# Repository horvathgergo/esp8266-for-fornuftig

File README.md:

Newer version of the board based on an ESP32-C6 chip is available here: https://github.com/horvathgergo/esp32c6-for-fornuftig

# Smart Air Purifier (Project Fornuftig)

Custom PCB based on ESP12-F (ESP8266) wifi module that serves as a smart controller for IKEA Fornuftig Air Purifiers. It's embedded microcontroller enables you to incorporate your device to home automation systems (preferably to Home Assistant) or control it via custom mobile applications as it enjoys support from wide variety of firmwares. This project has been implemented in KiCad (hardware) and in Micropython (sofware).

About IKEA Fornuftig: It's a compact, 31x45 cm air purifier launched in the market around 2020. It effectively cleans the indoor air from harmful PM2.5 particles and pollen for a reasonable price (approx. EUR60). The device is optimised for medium-sized bedrooms and has three fan speed. 

Current status of the development: **Finalized**

Hardware: 
* [x] Schematic
* [x] Layout
* [x] BOM, CPL
* [x] 3D model 
* [x] Testing (v1.1 w/o switch)

Software:
* [x] MicroPython

## Hardware

PCB is a bit larger than the original one (98x40 mm) with mounting holes placed on it, thus it is supposed to fit just fine inside the plastic housing. Power supply of the fan is +24V, 0.8A. The board has a MC34063DR switching voltage regulator that provides the necessary power (+3v3, avg 70mA, peak >500mA) for the wifi module. This version (v2.0) of the board is designed with a rotary switch. To avoid unnecessary costs and save some space on the board physical filter reset button is not incorporated in this version as this function can be easily achieved through software side. 

The Purifier has a 4-pin PWM fan with +24VDC, 0.5A. The pins are power, ground, clk, fg. Clk is a control pin and fg is the tacho pin for feedback purposes. The fan operates with a constant duty cycle of 50% and variable frequency between ca. 1-300Hz.

MCU programming: the board supports only UART programming via TX, RX pin headers (as no USB interface), thus USB to TTL converter is necessary to upload your firmware. It is recommended to supply the module via VIN and GND pins during initial setup. It is compatible with +5-24V supply (note: in serial bootloader mode you need to supply at least +5V. Standard +3v3 won't work as you may experience some voltage drop via the buck converter so make sure to provide enough voltage during flashing. Supplying +5V won't hurt the ESP as the VIN pin of the board is not directly connected to chip). Boot button is located on the right side of the wifi module.

Tested first version of the board w/o rotary switch:

BOM: Most of the chosen components are considered to be basic/standard parts at LCSC, however there are some extended components on the list (two large caps, inductor, esp, jst connectors and uart pin headers).

## Software

The software for Fornuftig has been developed in Micropython. It enables the device to be controlled via mqtt while exploits Home Assistant mqtt autodiscovery features that provides with a smooth (almost zero config) setup process.

More detailed description is available in this repo: https://github.com/horvathgergo/uPurifier

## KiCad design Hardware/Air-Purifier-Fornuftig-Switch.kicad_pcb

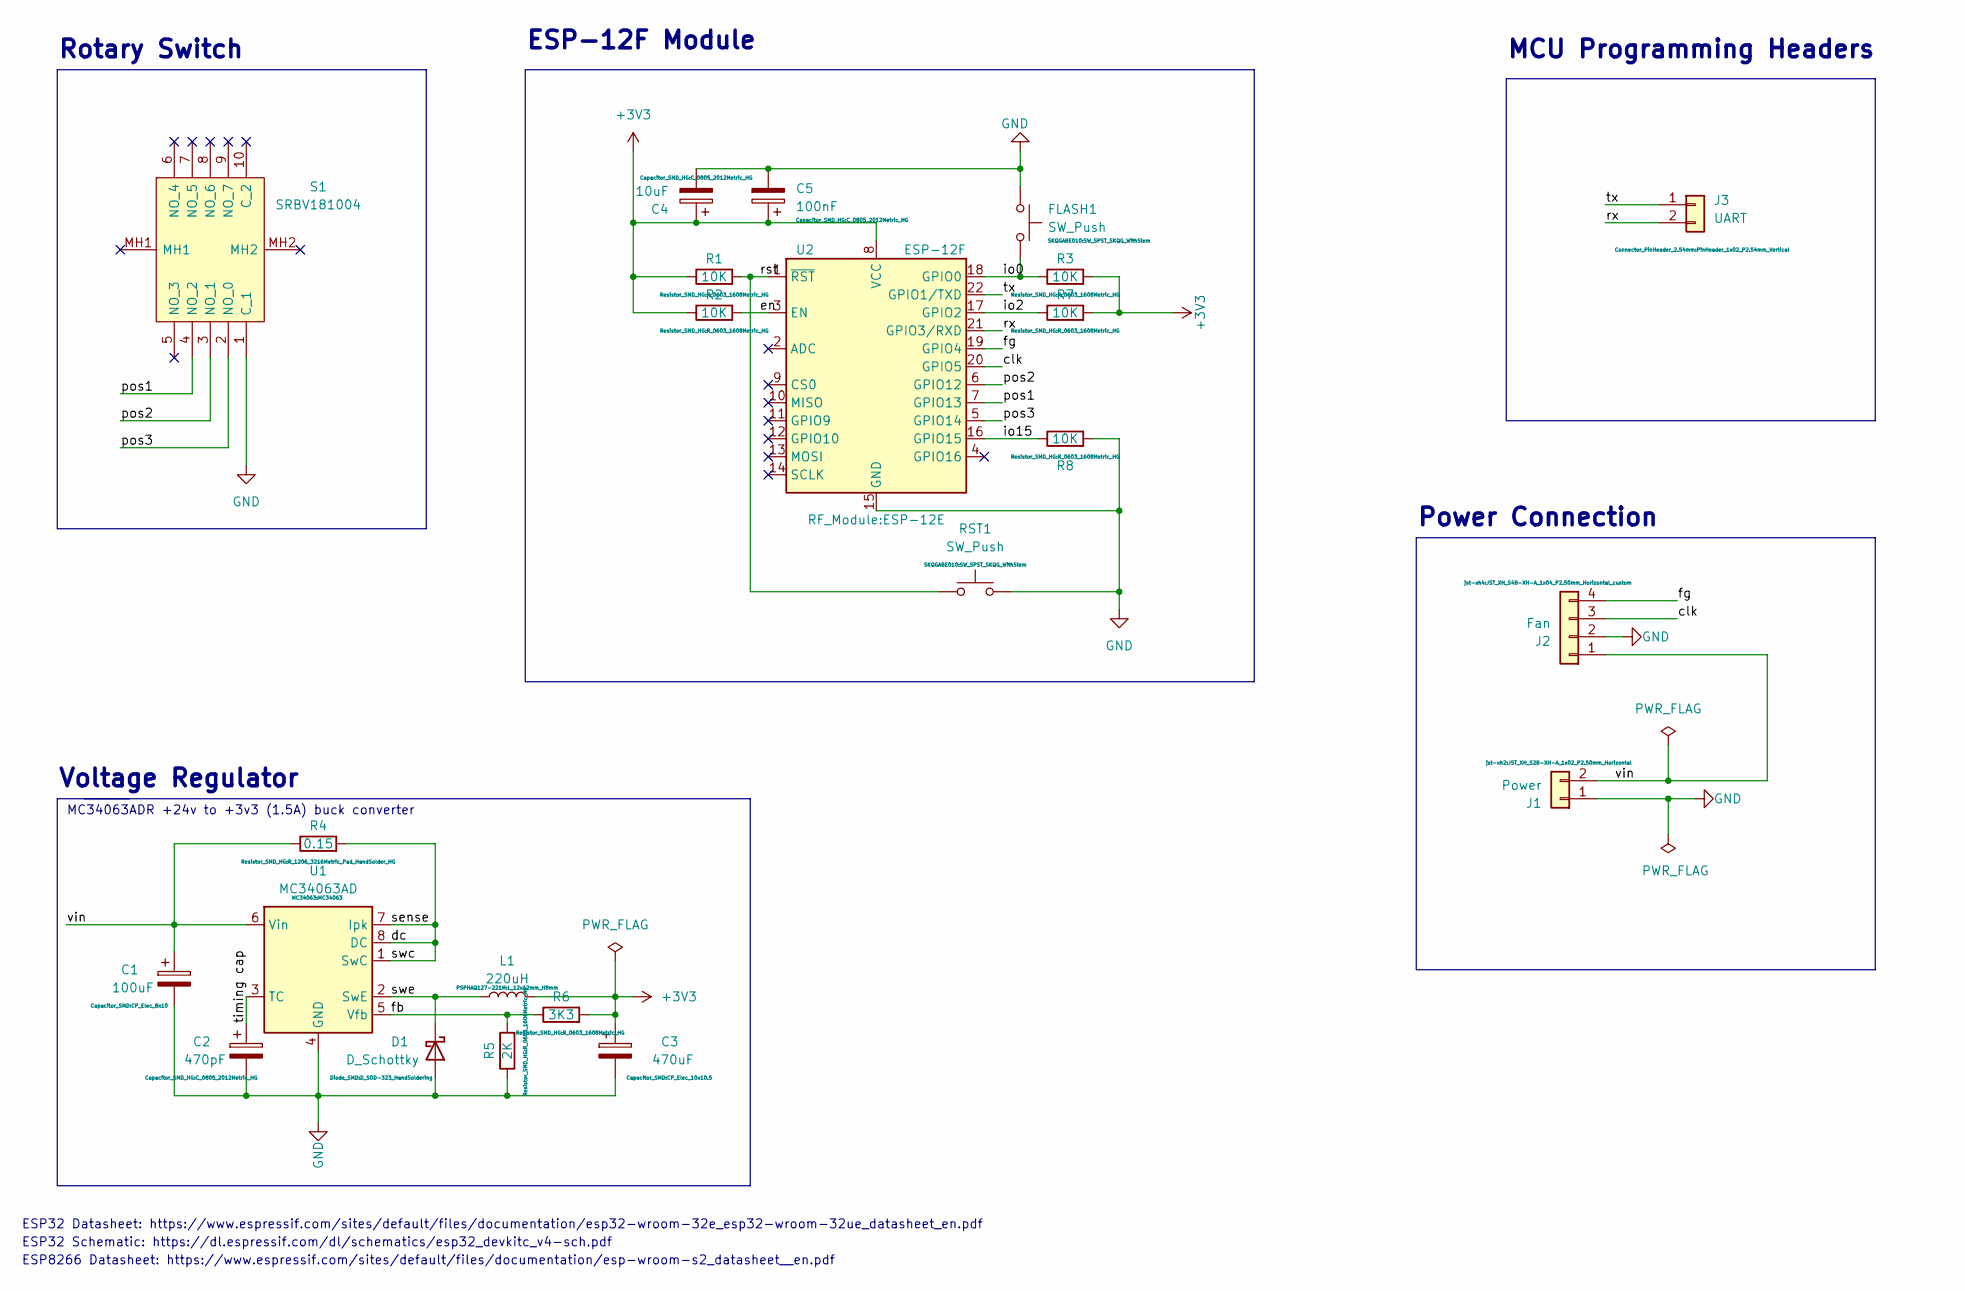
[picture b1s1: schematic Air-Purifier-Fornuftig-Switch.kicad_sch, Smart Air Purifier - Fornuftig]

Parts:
C1: 100uF; CP_Elec_8x10; LCSC C445063
C2: 470pF; C_0805_2012Metric_HG; LCSC C1743
C3: 470uF; CP_Elec_10x10.5; LCSC C72518
C4: 10uF; C_0805_2012Metric_HG; LCSC C15850
C5: 100nF; C_0805_2012Metric_HG; LCSC C28233
D1: D_Schottky; D_SOD-323_HandSoldering; LCSC C191023
FLASH1: SW_Push; SW_SPST_SKQG_WithStem; LCSC C318884
J1: Power; JST_XH_S2B-XH-A_1x02_P2.50mm_Horizontal
J2: Fan; JST_XH_S4B-XH-A_1x04_P2.50mm_Horizontal_custom
J3: UART; PinHeader_1x02_P2.54mm_Vertical
L1: 220uH; L_12x12mm_H8mm; LCSC C10151
R1, R2, R3, R7, R8: 10K; R_0603_1608Metric_HG; LCSC C25804
R4: 0.15; R_1206_3216Metric_Pad_HandSolder_HG; LCSC C247454
R5: 2K; R_0603_1608Metric_HG; LCSC C22975
R6: 3K3; R_0603_1608Metric_HG; LCSC C22978
RST1: SW_Push; SW_SPST_SKQG_WithStem; LCSC C318884
S1: SRBV181004; SRBV141404; Manufacturer_Part_Number SRBV181004; Mouser Part Number 688-SRBV181004
U1: MC34063AD; MC34063; LCSC C32078
U2: ESP-12F; ESP-12E; LCSC C82891

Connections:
+3V3: C3.1, C4.1, C5.1, L1.2, R1.1, R2.1, R3.2, R6.2, R7.2, U2.8 (VCC)
/clk: J2.3, U2.20 (GPIO5)
/dc: R4.2, U1.1 (SwC), U1.7 (Ipk), U1.8 (DC)
/en: R2.2, U2.3 (EN)
/fb: R5.2, R6.1, U1.5 (Vfb)
/fg: J2.4, U2.19 (GPIO4)
/io0: FLASH1.2, R3.1, U2.18 (GPIO0)
/io2: R7.1, U2.17 (GPIO2)
/io15: R8.1, U2.16 (GPIO15)
/pos1: S1.4 (NO_2), U2.7 (GPIO13)
/pos2: S1.3 (NO_1), U2.6 (GPIO12)
/pos3: S1.2 (NO_0), U2.5 (GPIO14)
/rst: R1.2, RST1.1, U2.1 (~RST)
/rx: J3.2, U2.21 (GPIO3/RXD)
/swe: D1.1 (K), L1.1, U1.2 (SwE)
/timing cap: C2.1, U1.3 (TC)
/tx: J3.1, U2.22 (GPIO1/TXD)
/vin: C1.1, J1.2, J2.1, R4.1, U1.6 (Vin)
GND: C1.2, C2.2, C3.2, C4.2, C5.2, D1.2 (A), FLASH1.1, J1.1, J2.2, R5.1, R8.2, RST1.2, S1.1 (C_1), U1.4 (GND), U2.15 (GND)

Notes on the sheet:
Rotary Switch
ESP32 Schematic: https://dl.espressif.com/dl/schematics/esp32_devkitc_v4-sch.pdf
MC34063ADR +24v to +3v3 (1.5A) buck converter
ESP-12F Module
ESP8266 Datasheet: https://www.espressif.com/sites/default/files/documentation/esp-wroom-s2_datasheet__en.pdf
ESP32 Datasheet: https://www.espressif.com/sites/default/files/documentation/esp32-wroom-32e_esp32-wroom-32ue_datasheet_en.pdf
MCU Programming Headers
Power Connection
Voltage Regulator

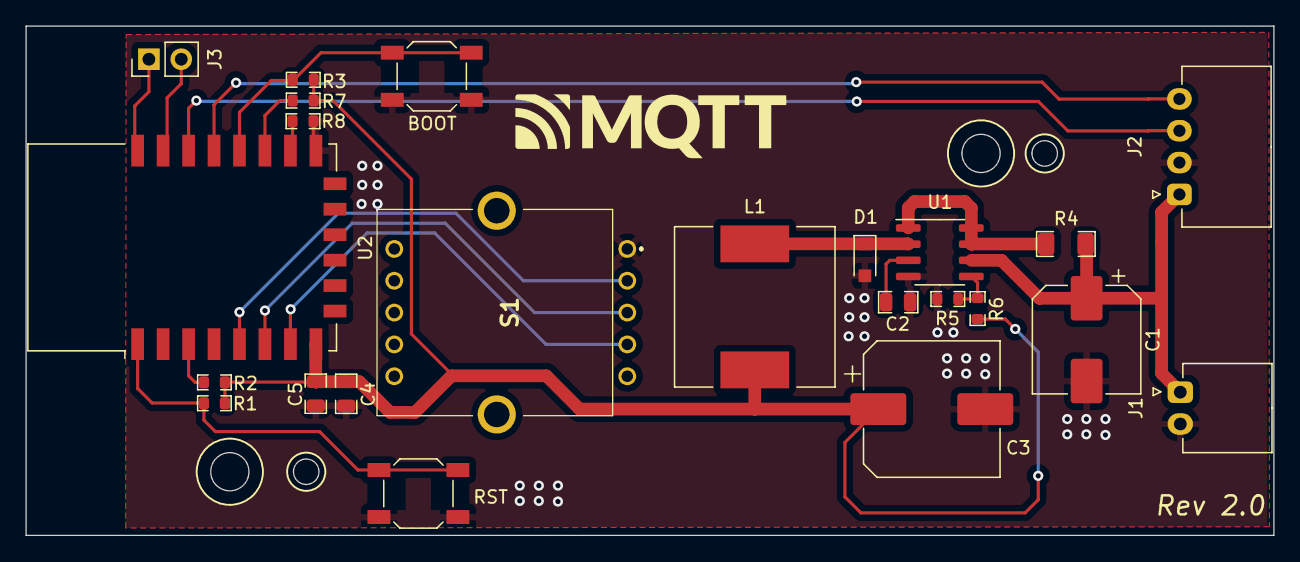
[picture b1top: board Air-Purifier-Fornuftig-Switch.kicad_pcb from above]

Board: 2 copper layers, 98.0 x 40.0 mm, 23 parts (0 on the bottom side), 19 nets.

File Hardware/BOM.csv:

Comment,Designator,Footprint,LCSC Part Number,
470pF,C2,Capacitor_SMD_HG:C_0805_2012Metric_HG,C1743,
10uF,C4,Capacitor_SMD_HG:C_0805_2012Metric_HG,C15850,
100nF,C5,Capacitor_SMD_HG:C_0805_2012Metric_HG,C28233,
D_Schottky,D1,Diode_SMD:D_SOD-323_HandSoldering,C191023,
SW_Push,"FLASH1, RST1",SKQGABE010:SW_SPST_SKQG_WithStem,C318884,
10K,"R1, R2, R3, R7, R8",Resistor_SMD_HG:R_0603_1608Metric_HG,C25804,
2K,R5,Resistor_SMD_HG:R_0603_1608Metric_HG,C22975,
3K3,R6,Resistor_SMD_HG:R_0603_1608Metric_HG,C22978,
MC34063AD,U1,MC34063:MC34063,C32078,
ESP-12F,U2,RF_Module:ESP-12E,C82891,

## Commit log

2023-01-30 add v1.1 3D models
2023-01-30 Add BOM, CPL, Gerber
2023-01-30 Add Schematic-v1.1
2023-02-06 Update README.md
    Minor fix
2023-03-13 add v2.0 3D model
2023-03-13 add v2.0 KiCad
2023-03-13 add layout v2.0
2023-03-13 add Schematic v2.0
